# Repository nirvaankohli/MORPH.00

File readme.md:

# MORPH.00

---

MORPH.00 is a keyboard with 6 key switches and a rotary encoder that can change(morph their function). It also has an OLED to display each key or encoder's function at any given time. It is powered by the RP2040!

---

## Why choose this project?

When I initially found about fallout, I knew it was an one in a lifetime opportunity. I also knew that I did not know anything about hardware. So I looked online and on youtube and decided that a macropad was perfect for me. After a few days of brainstorming, I decided to settle for the best balance between challenging and easy(this project). Also it was pretty cool, cus like who would not want a keyboard that can change functions based on the app you are on to make work less repetitive. The use for this is legitimate because I can think of so many times in a day I press the same 6 button when in app. This would be really useful for myself, and that's why I chose to build it. Also a keyboard with a screen is rlly cool.

---

Looking back, this project was filled with a lot of firsts. I also had so much fun. Like who knew how relaxing some parts could be and how enraging others could be. Anyways, I learned my first real CAD software, onshape. I will definitely be using it in VEX Robotics as most of our team's CAD team seniored out. It took me some time to get comfortable but it is pretty cool. It was also my first time with KiCad. Making the schematic was interesting, pcb routing was so relaxing, but the errors sadly was not.

--- 

## A Little Summary

The keyboard is powered by a RP2040 on a [KB2040 Microcontroller](https://www.adafruit.com/product/5302?srsltid=AfmBOoqLa_n90N7_AYh5a78pJlOBana2qBx5fNuULukl6r5Ai2WtEuWO) running CircuitPython with many adafruit libraries. This is stuffed on the bottom-right side of the pcb board/keyboard and is the reason for it's goofy shape and proportions.

The six switches are Cherry MXs, the rotary encoder an EC11 Rotary Encoder, and the OLED a 5.5 Inch 256x64 display. There is also a part of this project on the host computer that sends info like key, encoder, or OLED changes to the keyboard.

--- 

# CAD Renderings

CAD was a very infuriating experience if I may add.

---

## PCB + Schematic

This is my final schematic

This schematic went through multiple, multiple changes. Like when I had to add power symbols, make a denouncer circuit, custom design the OLED symbol like 2 times, and change the GPIO pins for my OLED. I liked this portion a lot actually.

### Final PCB

I added a lot of stuff bc the Internet said so :). So hopefully that was not a mistake. I was also just informed no 90 or acute angles so maybe not so final pcb :(.

----

### How to Use It?

This is relatively easy to use assuming it is all put together and well. All you need to do is drag firmware/software files into the KB2040 and let the host computer code run as a background process.

The computer process will be listening on a port. From there you can read the documentation available in code/keyboard/ on how to automate the OLED, switches, and encoder functions. 

From there, it is just using the macropad as a macropad.

---

# How to construct it?

Since I have not had the pleasure of constructing this, I can't tell you for sure but below is how to build it if everything goes as planned.

1. Soldering Components
   1. This step assumes you have bought everything in the BOM.
   2. The first step is to solder all the components on to the PCB.
      1. Use the various KiCad files as reference to know where to put components if you are confused.
2. 3D Printing Case
   1. This again assumes you have a 3D printer or some way to get your hands on a physical version of the case(files in /cad).
   2. This is pretty self-explanatory as you need to obtain all 3D printed objects in cad/print.
3. Assembling the Body of the Macropad
   1. Use M3 screws and nylocks to fasten the OLED on to the PCB plate.
   2. Put the top plate on the board.
   3. It should click into place thanks to the Cherry MX switches.
   4. Slide your usb c cable through the hole on the side of the case. For future use plug that cable into your host computer.
   5. Then take your 3mm Spacer and insert it between the bottom of the PCB and plate
   6. Insert the screw on the bottom of the bottom plate 
   7. On the top of the pcb plate place a M3 nylock and fasten.
   8. Repeat for all other 3 corners.
   9. For extra precaution optionally add some type of adhesive between the top plate's side and the bottom plate's edges.
4. Add Keycaps and Cover for Encoder
   1. Start by putting a keycap on one of the switches. The keycap should slide in and click.
   2. Repeat for the remaining 5 keycaps.
   3. For the Rotary Encoder, simply press down the rotary encoder cover on the Rotary Encoder, and with some force it should slide in.

---

Congrats! You have know constructed MORPH.00. Hopefully it should work.

---

# BOM

Check `bom.csv`!

---

# Onshape Link

[Onshape](https://cad.onshape.com/documents/fb2e845d06a2abfe6a4c7c6e/w/d1b8caaf10144fcbff733afe/e/741c88277487ad0443e0a772?renderMode=0&uiState=69e956052d35c8d037460b8d)

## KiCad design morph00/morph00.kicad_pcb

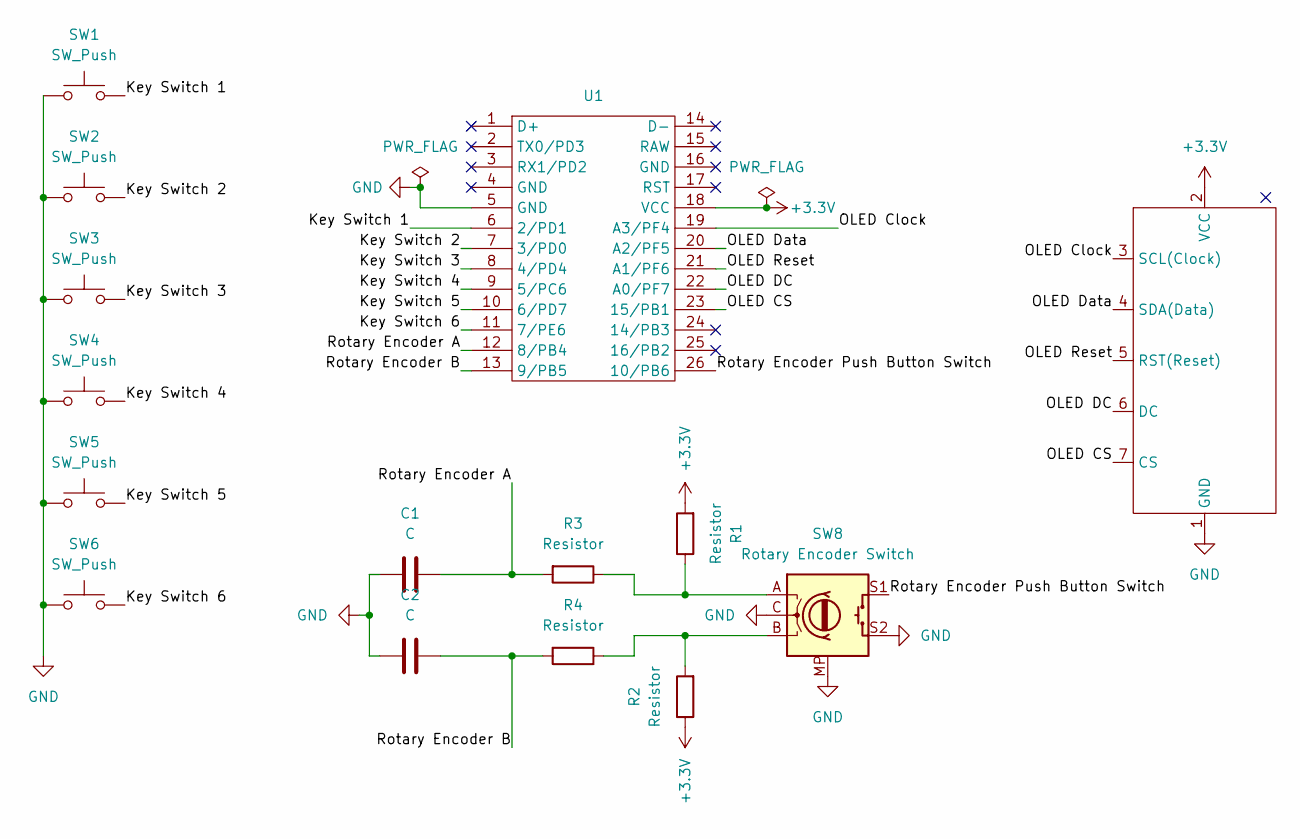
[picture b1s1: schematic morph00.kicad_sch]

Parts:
C1, C2: C; C_Disc_D5.0mm_W2.5mm_P2.50mm
DS1: TZT_5.5_OLED_SSD1322
R1, R2, R3, R4: Resistor; R_Axial_DIN0207_L6.3mm_D2.5mm_P7.62mm_Horizontal
SW1, SW2, SW3, SW4, SW5, SW6: SW_Push; SW_Cherry_MX_1.00u_PCB
SW8: Rotary Encoder Switch; RotaryEncoder_Alps_EC11E-Switch_Vertical_H20mm
U1: Adafruit_KB2040

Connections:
+3.3V: DS1.2 (VCC), R1.2, R2.1, U1.18 (VCC)
/Key Switch 1: SW1.2, U1.6 (2/PD1)
/Key Switch 2: SW2.2, U1.7 (3/PD0)
/Key Switch 3: SW3.2, U1.8 (4/PD4)
/Key Switch 4: SW4.2, U1.9 (5/PC6)
/Key Switch 5: SW5.2, U1.10 (6/PD7)
/Key Switch 6: SW6.2, U1.11 (7/PE6)
/OLED CS: DS1.7 (CS), U1.23 (15/PB1)
/OLED Clock: DS1.3 (SCL(Clock)), U1.19 (A3/PF4)
/OLED DC: DS1.6 (DC), U1.22 (A0/PF7)
/OLED Data: DS1.4 (SDA(Data)), U1.20 (A2/PF5)
/OLED Reset: DS1.5 (RST(Reset)), U1.21 (A1/PF6)
/Rotary Encoder A: C1.1, R3.2, U1.12 (8/PB4)
/Rotary Encoder B: C2.1, R4.2, U1.13 (9/PB5)
/Rotary Encoder Push Button Switch: SW8.S1, U1.26 (10/PB6)
GND: C1.2, C2.2, DS1.1 (GND), SW1.1, SW2.1, SW3.1, SW4.1, SW5.1, SW6.1, SW8.C, SW8.MP, SW8.S2, U1.5 (GND)
unnamed: R1.1, R3.1, SW8.A
unnamed: R2.2, R4.1, SW8.B

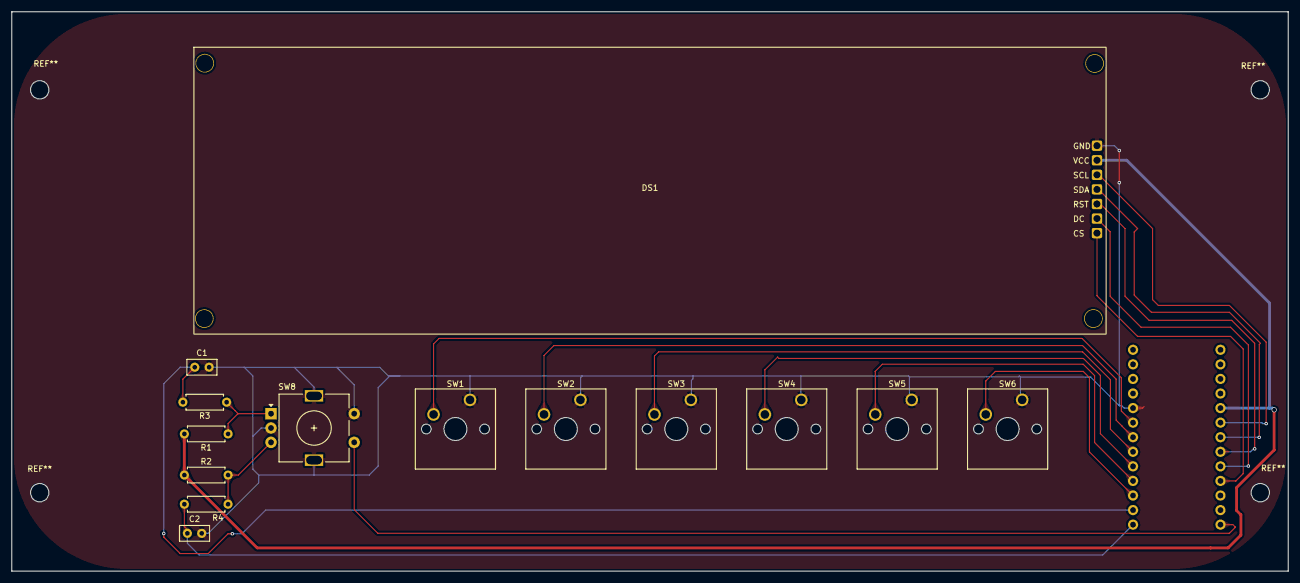
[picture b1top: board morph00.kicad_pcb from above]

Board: 2 copper layers, 222.5 x 97.5 mm, 15 parts (0 on the bottom side), 18 nets.

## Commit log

2026-03-29 Researched some components to use
2026-03-29 Just decideing components
2026-03-30 KICAD FILes
2026-03-30 FIGMA
2026-03-31 Changed some stuff
2026-04-20 Readme abt to add onshape files
2026-04-20 Added CAD files from Onshape including electrical components models, 3D print finals, and assemblies.
2026-04-21 code and pcb changes and docs
2026-04-22 I think im done
2026-04-22 changed zine name
2026-04-22 Stuff
2026-04-22 Final Commit hopefully
2026-05-04 Restructuring
2026-05-04 Uodate for final submission
